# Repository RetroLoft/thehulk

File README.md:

# TheHulk

Network and SD card storage cartridge for the Atari ST, STE, Mega ST(E), TT and Falcon,
built around an ESP32-S3 and a Lattice iCE40UP5K FPGA. Successor of SideTNFS.

## Repository layout

| Path | Contents |
|---|---|
| `hardware/dev-v2/` | KiCad project and JLCPCB production files of the development board (ESP32-S3-DevKitC) |
| `hardware/prod-v2/` | KiCad project of the production board (ESP32-S3 module on the board, native USB, not ordered yet) |
| `hardware/prod-v3/` | prod-v2 plus switched 5 V on the micro-USB port, for USB keyboards and mice through an OTG adapter (not ordered yet, no firmware support yet) |
| `fpga/` | FPGA gateware (Verilog), pin constraints, simulation |
| `esp32/` | ESP32-S3 firmware (ESP-IDF); embeds the bitstream, GEMDRIVE and the built-in files of the flash drive |
| `atari/gemdrive/` | GEMDRIVE: the cartridge code the Atari runs (68000 assembly) |
| `atari/config/` | Configuration program for the Atari (GEM, C) |
| `atari/sting/` | `CART_NET.STX`: STinG driver for TheHulk's network bridge (C) |
| `atari/stingins/` | `STINGINS.TOS`: STinG installer on the flash drive, see [docs/NETWORK.md](docs/NETWORK.md) |
| `tools/` | Development helpers |
| `docs/` | Documentation: [hardware](docs/hardware-v2.md), [drives](docs/DRIVES.md), [internet with STinG](docs/NETWORK.md), [web page](docs/WEB.md), [cartridge emulator](docs/CARTRIDGE.md), [floppy emulator](docs/FLOPPY.md) |

## Building

```
./build.sh                     # everything
./build.sh flash /dev/ttyACM0  # and flash the ESP32, then open the serial monitor
./build.sh sim                 # gateware simulation
```

Requirements:
- FPGA: yosys, nextpnr-ice40 and icepack. `build.sh` installs the YoWASP builds from PyPI in
  `.venv-fpga` when no native tools are found.
- GEMDRIVE: `stcmd` from atarist-toolkit-docker (Docker image `logronoide/atarist-toolkit-docker`).
- Configuration program: `m68k-atari-mint-gcc` with gemlib. STinG driver and installer:
  `m68k-atari-mint-gcc`.
- ESP32: ESP-IDF 5.5 in `~/esp/esp-idf` (or set `IDF_PATH`).

## How it works

1. The ESP32 waits until the Atari powers the FPGA side of the board, then loads the
   bitstream into the FPGA over SPI (~50 ms at 20 MHz).
2. It writes the cartridge image (GEMDRIVE) into the FPGA's SPRAM and enables the cartridge.
   The FPGA keeps the data bus updated with the word at the current address; the data
   buffer is enabled in hardware by /ROM3 or /ROM4.
3. When the Atari is switched off, the ESP32 drives all FPGA lines low and waits for the
   next power-up.

Status LED (on the DevKitC): see [docs/WEB.md](docs/WEB.md#the-status-led). The web page
(`http://thehulk.local/`) shows the state and all settings; button 1 held 10 s switches AP
mode on, TheHulk's own Wi-Fi network for use away from home.

## License

GPL-3.0, see [LICENSE](LICENSE). GEMDRIVE is based on the SidecarTridge Multi-device
project by Diego Parrilla Santamaría (GOODDATA LABS SL).

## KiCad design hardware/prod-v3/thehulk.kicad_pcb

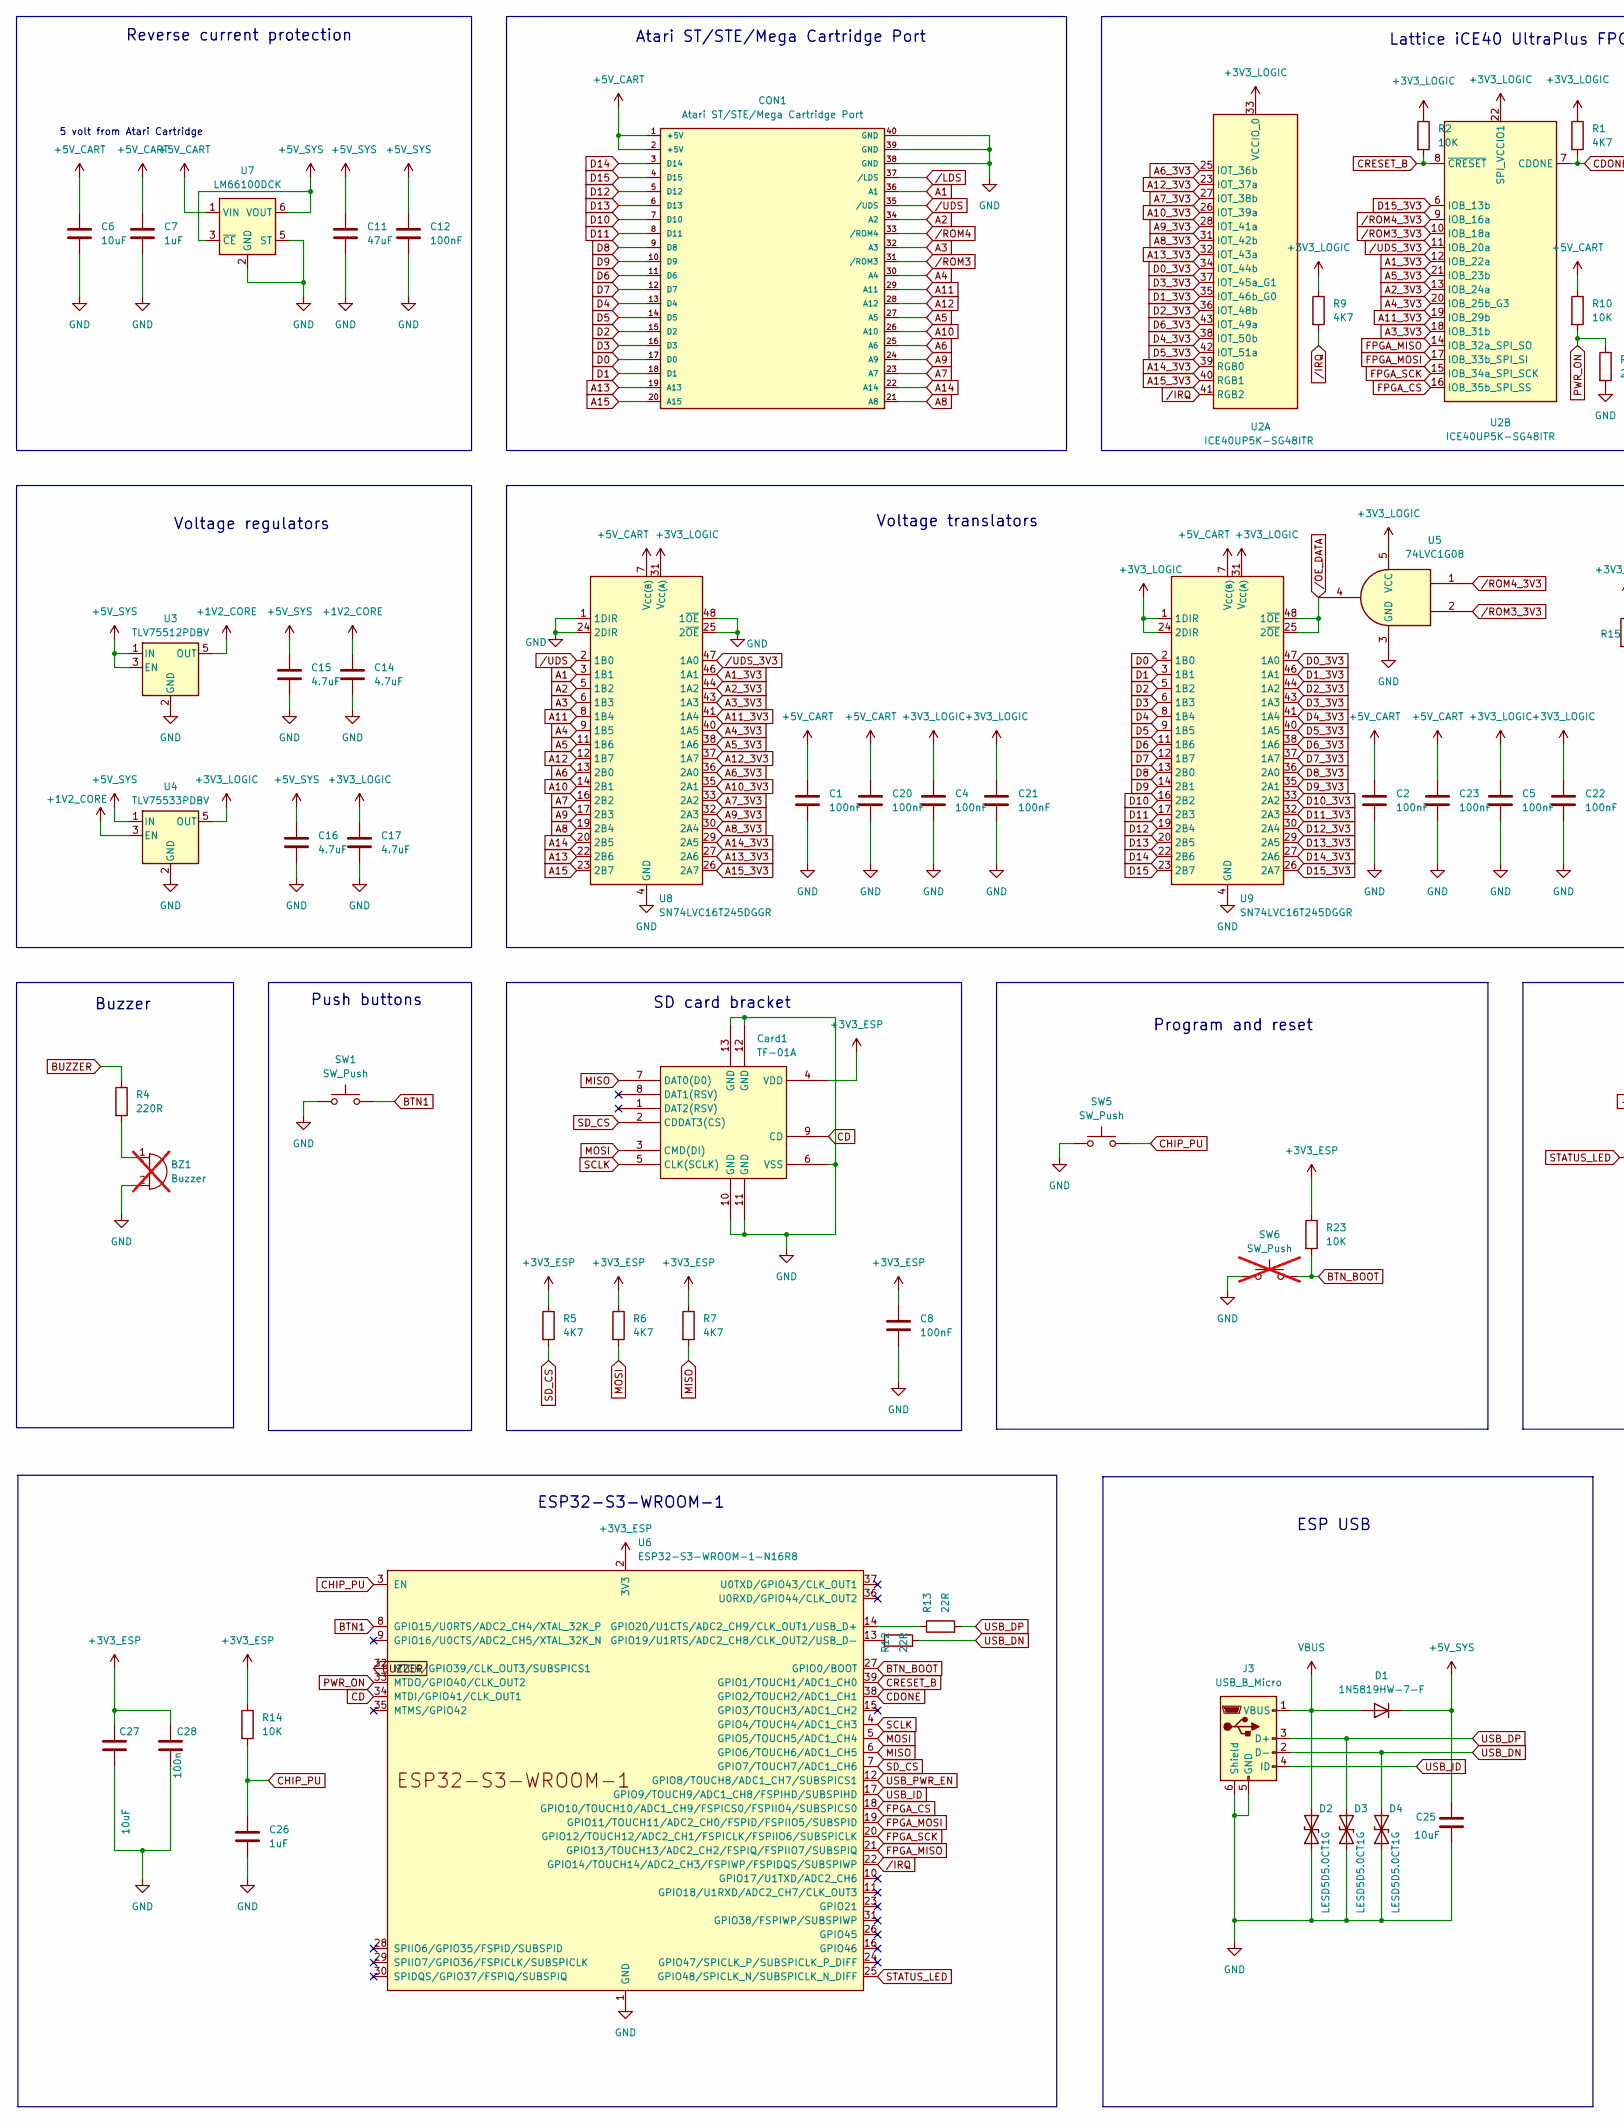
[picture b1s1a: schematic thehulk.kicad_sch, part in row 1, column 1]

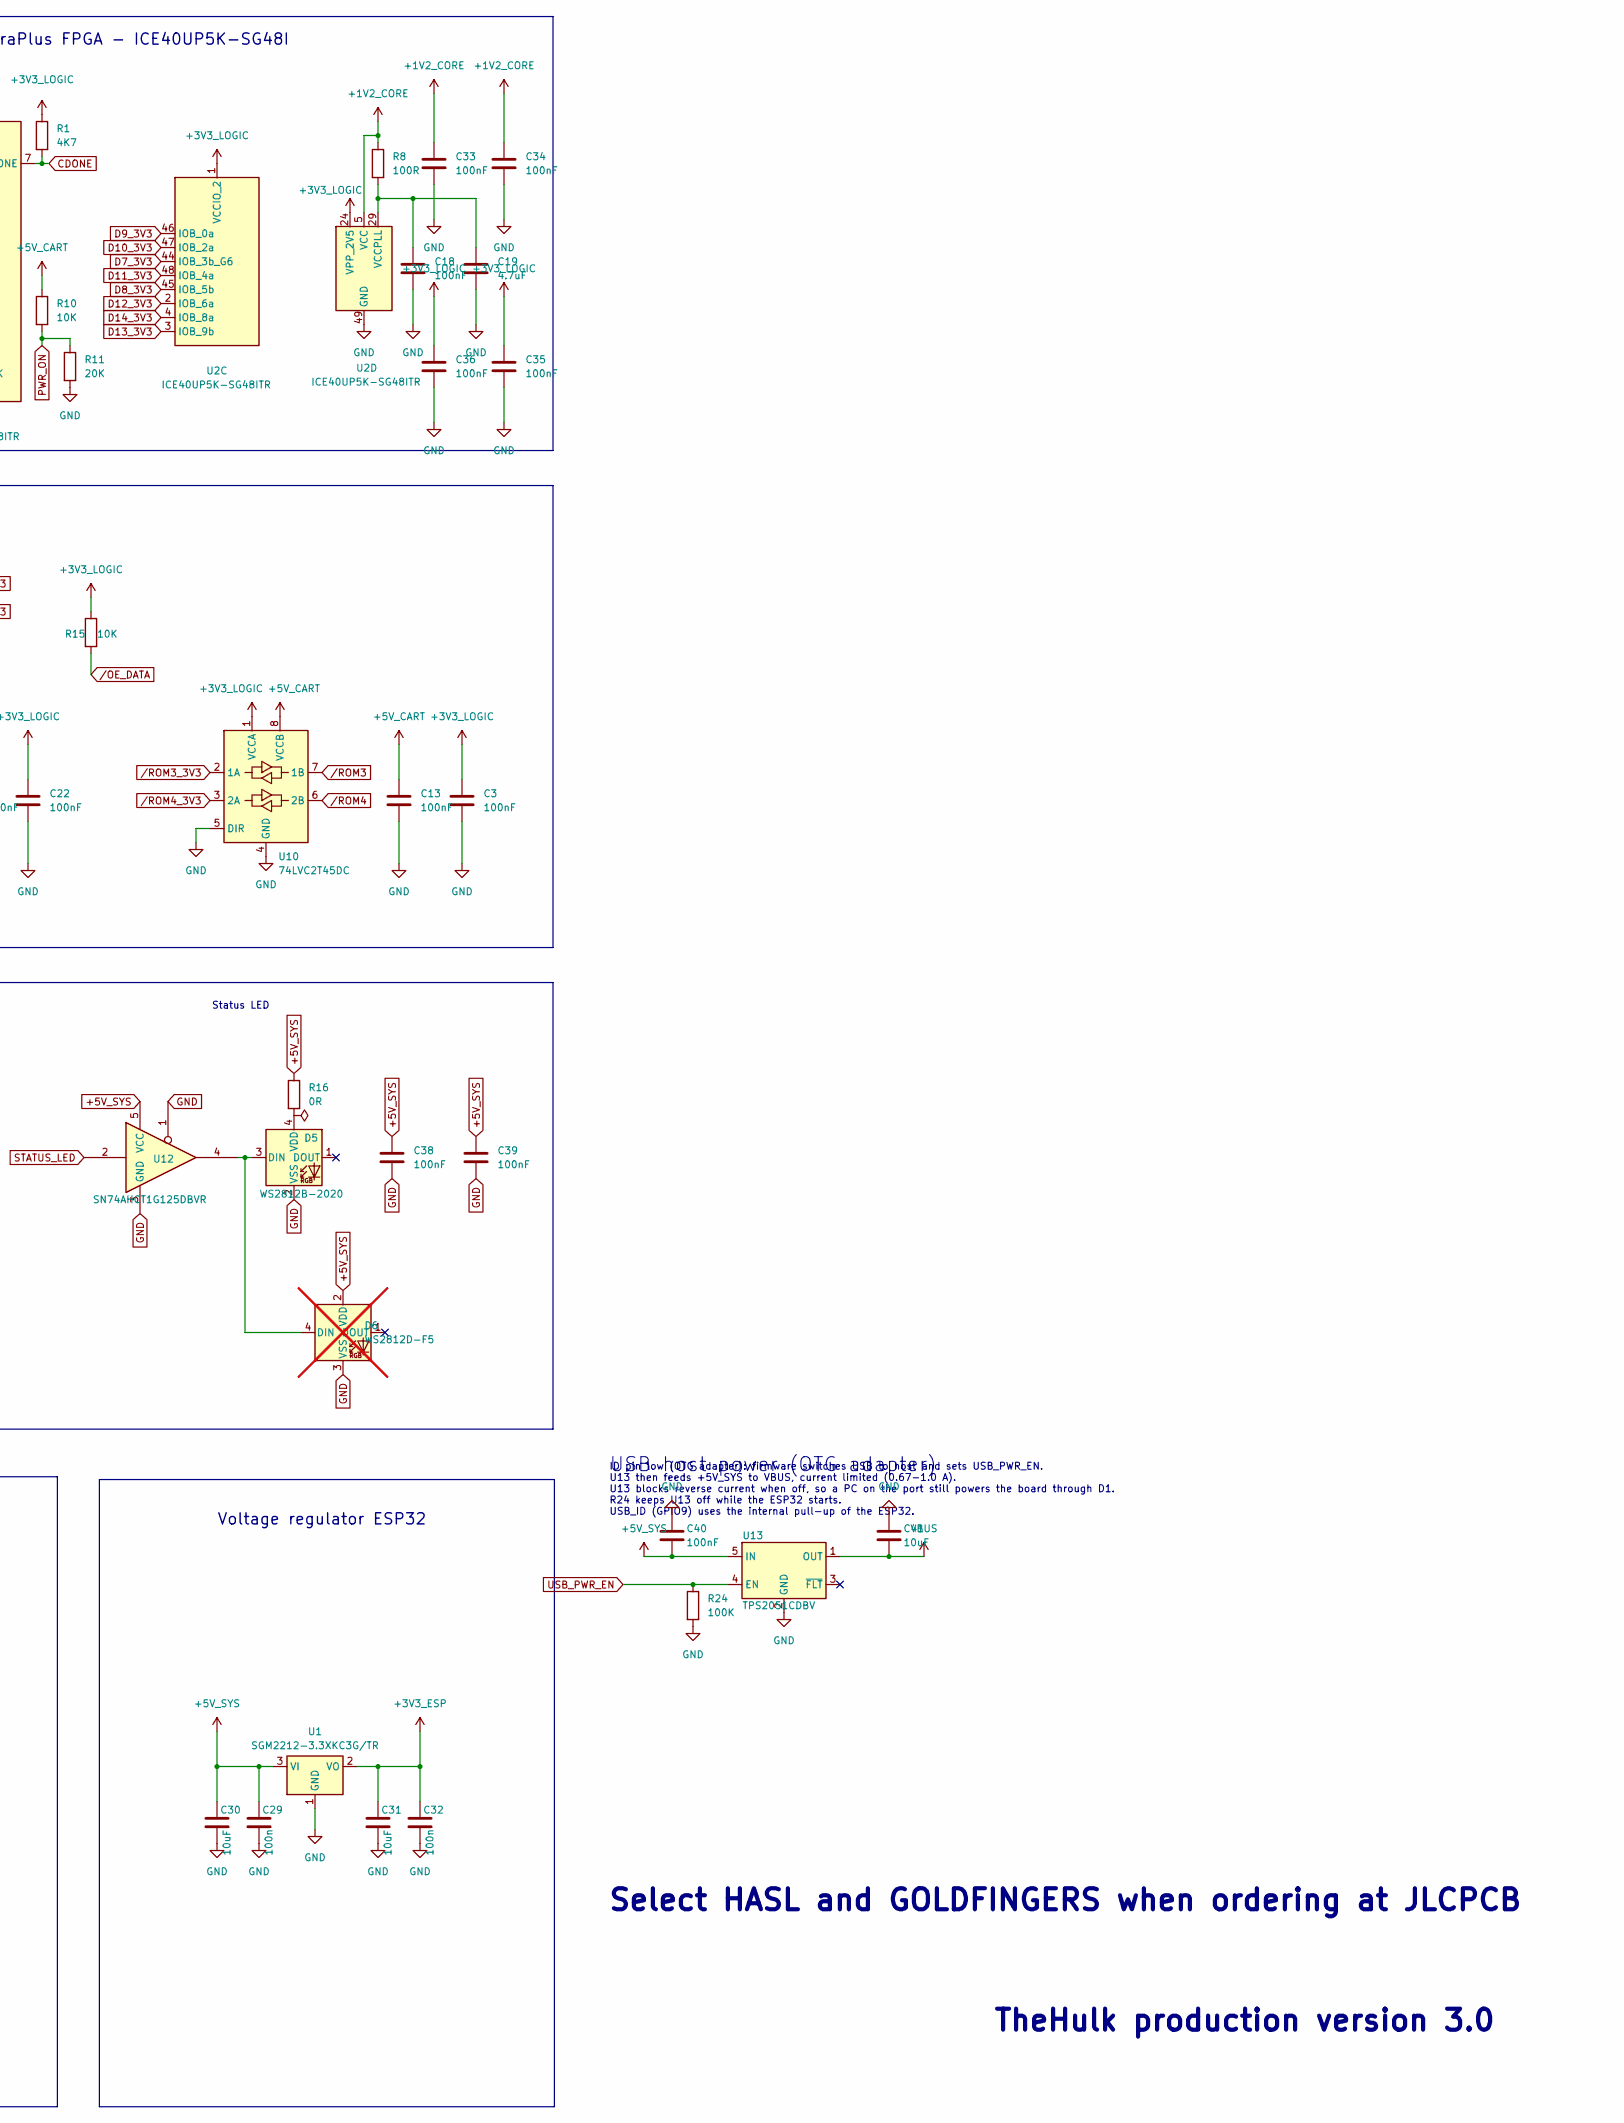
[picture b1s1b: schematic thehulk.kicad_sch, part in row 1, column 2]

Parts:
BZ1: Buzzer; Buzzer_12x9.5RM7.6; not fitted
C1, C2, C3, C4, C5, C8, C12, C13, C18, C20, C21, C22, C23, C33, C34, C35, C36, C38, C39, C40: 100nF; C_0402_1005Metric; LCSC Part C1525
C6, C25, C27, C30, C31, C41: 10uF; C_0603_1608Metric; LCSC Part C19702
C7: 1uF; C_0402_1005Metric; LCSC Part C52923
C11: 47uF; C_0805_2012Metric; LCSC Part C16780
C14, C15, C16, C17, C19: 4.7uF; C_0603_1608Metric; LCSC Part C19666
C26: 1uF; C_0603_1608Metric; LCSC Part C15849
C28, C29, C32: 100n; C_0603_1608Metric; LCSC Part C14663
CON1: Atari ST/STE/Mega Cartridge Port; Atari_Cart_Edge_40P_2mm
Card1: TF-01A; TF-SMD_TF-01A; MPN TF-01A; LCSC Part C91145
D1: 1N5819HW-7-F; D_SOD-123; LCSC Part C82544
D2, D3, D4: LESD5D5.0CT1G; D_SOD-523; LCSC Part C5199850
D5: WS2812B-2020; LED_WS2812B-2020_PLCC4_2.0x2.0mm; LCSC Part C52917434
D6: WS2812D-F5; LED_D5.0mm-4_WS2812D-F5; LCSC Part C190565; not fitted
J3: USB_B_Micro; USB_Micro-B_C10418; MPN Jing Extension 920-E52A2021S10100; LCSC Part C10418
R1, R5, R6, R7, R9: 4K7; R_0402_1005Metric; LCSC Part C25900
R2, R10: 10K; R_0402_1005Metric; LCSC Part C25744
R4: 220R; R_0603_1608Metric; LCSC Part C22962
R8: 100R; R_0402_1005Metric; LCSC Part C25076
R11: 20K; R_0402_1005Metric; LCSC Part C25765
R12, R13: 22R; R_0402_1005Metric; LCSC Part C25092
R14, R15, R23: 10K; R_0603_1608Metric; LCSC Part C25804
R16: 0R; R_0805_2012Metric; LCSC Part C17477
R24: 100K; R_0402_1005Metric; LCSC Part C25741
SW1: SW_Push; SW_Tactile_6x6_SMD_H9.5; MPN Kinghelm KH-6X6X9.5H-SMT (9.5 mm); LCSC Part C3038675
SW5: SW_Push; SW_SPST_B3U-1000P; LCSC Part C231329
SW6: SW_Push; SW_SPST_B3U-1000P; LCSC Part C231329; not fitted
U1: SGM2212-3.3XKC3G/TR; SOT-223-3_TabPin2; LCSC Part C3294699
U2: ICE40UP5K-SG48ITR; QFN-48-1EP_7x7mm_P0.5mm_EP5.6x5.6mm; LCSC Part C2678152
U3: TLV75512PDBV; SOT-23-5; LCSC Part C2877864
U4: TLV75533PDBV; SOT-23-5; LCSC Part C404027
U5: 74LVC1G08; SOT-23-5; LCSC Part C7666
U6: ESP32-S3-WROOM-1-N16R8; ESP32-S3-WROOM-1; LCSC Part C2913202
U7: LM66100DCK; SOT-363_SC-70-6; LCSC Part C2869734
U8, U9: SN74LVC16T245DGGR; TSSOP-48_6.1x12.5mm_P0.5mm; LCSC C148170
U10: 74LVC2T45DC; VSSOP-8_2.3x2mm_P0.5mm; LCSC Part C15741
U12: SN74AHCT1G125DBVR; SOT-23-5; LCSC Part C7484
U13: TPS2051CDBV; SOT-23-5; LCSC Part C129581

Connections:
+1V2_CORE: C14.1, C33.1, C34.1, R8.1, U2.5 (VCC), U2.30 (VCC), U3.5 (OUT), U4.3 (EN)
+3V3_ESP: C8.1, C27.1, C28.1, C31.1, C32.1, Card1.4 (VDD), R5.1, R6.1, R7.1, R14.1, R23.1, U1.2 (VO), U6.2 (3V3)
+3V3_LOGIC: C3.1, C4.1, C5.1, C17.1, C21.1, C22.1, C35.1, C36.1, R1.1, R2.1, R9.1, R15.1, U2.1 (VCCIO_2), U2.22 (SPI_VCCIO1), U2.24 (VPP_2V5), U2.33 (VCCIO_0), U4.5 (OUT), U5.5 (VCC), U8.31 (V_{CC(A)}), U8.42 (V_{CC(A)}), U9.1 (1DIR), U9.24 (2DIR), U9.31 (V_{CC(A)}), U9.42 (V_{CC(A)}), U10.1 (VCCA)
+5V_CART: C1.1, C2.1, C6.1, C7.1, C13.1, C20.1, C23.1, CON1.1 (+5V), CON1.2 (+5V), R10.1, U7.1 (VIN), U8.7 (V_{CC(B)}), U8.18 (V_{CC(B)}), U9.7 (V_{CC(B)}), U9.18 (V_{CC(B)}), U10.8 (VCCB)
+5V_SYS: C11.1, C12.1, C15.1, C16.1, C25.1, C29.1, C30.1, C38.1, C39.1, C40.2, D1.1 (K), D6.2 (VDD), R16.1, U1.3 (VI), U3.1 (IN), U3.3 (EN), U4.1 (IN), U7.3 (~CE), U7.6 (VOUT), U12.5 (VCC), U13.5 (IN)
A1: CON1.36 (A1), U8.3 (1B1)
A1_3V3: U2.12 (IOB_22a), U8.46 (1A1)
A2: CON1.34 (A2), U8.5 (1B2)
A2_3V3: U2.13 (IOB_24a), U8.44 (1A2)
A3: CON1.32 (A3), U8.6 (1B3)
A3_3V3: U2.18 (IOB_31b), U8.43 (1A3)
A4: CON1.30 (A4), U8.9 (1B5)
A4_3V3: U2.20 (IOB_25b_G3), U8.40 (1A5)
A5: CON1.27 (A5), U8.11 (1B6)
A5_3V3: U2.21 (IOB_23b), U8.38 (1A6)
A6: CON1.25 (A6), U8.13 (2B0)
A6_3V3: U2.25 (IOT_36b), U8.36 (2A0)
A7: CON1.23 (A7), U8.16 (2B2)
A7_3V3: U2.27 (IOT_38b), U8.33 (2A2)
A8: CON1.21 (A8), U8.19 (2B4)
A8_3V3: U2.31 (IOT_42b), U8.30 (2A4)
A9: CON1.24 (A9), U8.17 (2B3)
A9_3V3: U2.28 (IOT_41a), U8.32 (2A3)
A10: CON1.26 (A10), U8.14 (2B1)
A10_3V3: U2.26 (IOT_39a), U8.35 (2A1)
A11: CON1.29 (A11), U8.8 (1B4)
A11_3V3: U2.19 (IOB_29b), U8.41 (1A4)
A12: CON1.28 (A12), U8.12 (1B7)
A12_3V3: U2.23 (IOT_37a), U8.37 (1A7)
A13: CON1.19 (A13), U8.22 (2B6)
A13_3V3: U2.32 (IOT_43a), U8.27 (2A6)
A14: CON1.22 (A14), U8.20 (2B5)
A14_3V3: U2.39 (RGB0), U8.29 (2A5)
A15: CON1.20 (A15), U8.23 (2B7)
A15_3V3: U2.40 (RGB1), U8.26 (2A7)
BTN1: SW1.2, U6.8 (GPIO15/U0RTS/ADC2_CH4/XTAL_32K_P)
BTN_BOOT: R23.2, SW6.2, U6.27 (GPIO0/BOOT)
BUZZER: R4.1, U6.32 (MTCK/GPIO39/CLK_OUT3/SUBSPICS1)
CD: Card1.9 (CD), U6.34 (MTDI/GPIO41/CLK_OUT1)
CDONE: R1.2, U2.7 (CDONE), U6.38 (GPIO2/TOUCH2/ADC1_CH1)
CHIP_PU: C26.1, R14.2, SW5.2, U6.3 (EN)
CRESET_B: R2.2, U2.8 (~CRESET), U6.39 (GPIO1/TOUCH1/ADC1_CH0)
D0: CON1.17 (D0), U9.2 (1B0)
D0_3V3: U2.34 (IOT_44b), U9.47 (1A0)
D1: CON1.18 (D1), U9.3 (1B1)
D1_3V3: U2.35 (IOT_46b_G0), U9.46 (1A1)
D2: CON1.15 (D2), U9.5 (1B2)
D2_3V3: U2.36 (IOT_48b), U9.44 (1A2)
D3: CON1.16 (D3), U9.6 (1B3)
D3_3V3: U2.37 (IOT_45a_G1), U9.43 (1A3)
D4: CON1.13 (D4), U9.8 (1B4)
D4_3V3: U2.38 (IOT_50b), U9.41 (1A4)
D5: CON1.14 (D5), U9.9 (1B5)
D5_3V3: U2.42 (IOT_51a), U9.40 (1A5)
D6: CON1.11 (D6), U9.11 (1B6)
D6_3V3: U2.43 (IOT_49a), U9.38 (1A6)
D7: CON1.12 (D7), U9.12 (1B7)
D7_3V3: U2.44 (IOB_3b_G6), U9.37 (1A7)
D8: CON1.9 (D8), U9.13 (2B0)
D8_3V3: U2.45 (IOB_5b), U9.36 (2A0)
D9: CON1.10 (D9), U9.14 (2B1)
D9_3V3: U2.46 (IOB_0a), U9.35 (2A1)
D10: CON1.7 (D10), U9.16 (2B2)
D10_3V3: U2.47 (IOB_2a), U9.33 (2A2)
D11: CON1.8 (D11), U9.17 (2B3)
D11_3V3: U2.48 (IOB_4a), U9.32 (2A3)
D12: CON1.5 (D12), U9.19 (2B4)
D12_3V3: U2.2 (IOB_6a), U9.30 (2A4)
D13: CON1.6 (D13), U9.20 (2B5)
D13_3V3: U2.3 (IOB_9b), U9.29 (2A5)
D14: CON1.3 (D14), U9.22 (2B6)
D14_3V3: U2.4 (IOB_8a), U9.27 (2A6)
D15: CON1.4 (D15), U9.23 (2B7)
D15_3V3: U2.6 (IOB_13b), U9.26 (2A7)
FPGA_CS: U2.16 (IOB_35b_SPI_SS), U6.18 (GPIO10/TOUCH10/ADC1_CH9/FSPICS0/FSPIIO4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)
FPGA_MISO: U2.14 (IOB_32a_SPI_SO), U6.21 (GPIO13/TOUCH13/ADC2_CH2/FSPIQ/FSPIIO7/S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)
FPGA_MOSI: U2.17 (IOB_33b_SPI_SI), U6.19 (GPIO11/TOUCH11/ADC2_CH0/FSPID/FSPIIO5/S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)
FPGA_SCK: U2.15 (IOB_34a_SPI_SCK), U6.20 (GPIO12/TOUCH12/ADC2_CH1/FSPICLK/FSPIIO6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)
GND: BZ1.2 (-), C1.2, C2.2, C3.2, C4.2, C5.2, C6.2, C7.2, C8.2, C11.2, C12.2, C13.2, C14.2, C15.2, C16.2, C17.2, C18.2, C19.2, C20.2, C21.2, C22.2, C23.2, C25.2, C26.2, C27.2, C28.2, C29.2, C30.2, C31.2, C32.2, C33.2, C34.2, C35.2, C36.2, C38.2, C39.2, C40.1, C41.1, CON1.38 (GND), CON1.39 (GND), CON1.40 (GND), Card1.6 (VSS), Card1.10 (GND), Card1.11 (GND), Card1.12 (GND), Card1.13 (GND), D2.1 (A1), D3.1 (A1), D4.1 (A1), D5.2 (VSS), D6.3 (VSS), J3.5 (GND), J3.6 (Shield), R11.2, R24.2, SW1.1, SW5.1, SW6.1, U1.1 (GND), U2.49 (GND), U3.2 (GND), U4.2 (GND), U5.3 (GND), U6.1 (GND), U6.40 (GND), U6.41 (GND), U7.2 (GND), U7.5 (ST), U8.1 (1DIR), U8.4 (GND), U8.10 (GND), U8.15 (GND), U8.21 (GND), U8.24 (2DIR), U8.25 (2~OE), U8.28 (GND), U8.34 (GND), U8.39 (GND), U8.45 (GND), U8.48 (1~OE), U9.4 (GND), U9.10 (GND), U9.15 (GND), U9.21 (GND), U9.28 (GND), U9.34 (GND), U9.39 (GND), U9.45 (GND), U10.4 (GND), U10.5 (DIR), U12.1, U12.3 (GND), U13.2 (GND)
MISO: Card1.7 (DAT0(D0)), R7.2, U6.6 (GPIO6/TOUCH6/ADC1_CH5)
MOSI: Card1.3 (CMD(DI)), R6.2, U6.5 (GPIO5/TOUCH5/ADC1_CH4)
unnamed: BZ1.1 (+), R4.2
unnamed: D5.3 (DIN), D6.4 (DIN), U12.4
unnamed: D5.4 (VDD), R16.2
unnamed: C18.1, C19.1, R8.2, U2.29 (VCCPLL)
unnamed: R12.1, U6.13 (GPIO19/U1RTS/ADC2_CH8/CLK_OUT2/USB_D-)
unnamed: R13.1, U6.14 (GPIO20/U1CTS/ADC2_CH9/CLK_OUT1/USB_D+)
PWR_ON: R10.2, R11.1, U6.33 (MTDO/GPIO40/CLK_OUT2)
SCLK: Card1.5 (CLK(SCLK)), U6.4 (GPIO4/TOUCH4/ADC1_CH3)
SD_CS: Card1.2 (CDDAT3(CS)), R5.2, U6.7 (GPIO7/TOUCH7/ADC1_CH6)
STATUS_LED: U6.25 (GPIO48/SPICLK_N/SUBSPICLK_N_DIFF), U12.2
USB_DN: D4.2 (A2), J3.2 (D-), R12.2
USB_DP: D3.2 (A2), J3.3 (D+), R13.2
USB_ID: J3.4 (ID), U6.17 (GPIO9/TOUCH9/ADC1_CH8/FSPIHD/SUBSPIHD)
USB_PWR_EN: R24.1, U6.12 (GPIO8/TOUCH8/ADC1_CH7/SUBSPICS1), U13.4 (EN)
VBUS: C41.2, D1.2 (A), D2.2 (A2), J3.1 (VBUS), U13.1 (OUT)
/IRQ: R9.2, U2.41 (RGB2), U6.22 (GPIO14/TOUCH14/ADC2_CH3/FSPIWP/FSPIDQS/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)
/LDS: CON1.37 (/LDS)
/OE_DATA: R15.2, U5.4, U9.25 (2~OE), U9.48 (1~OE)
/ROM3: CON1.31 (/ROM3), U10.7 (1B)
/ROM3_3V3: U2.10 (IOB_18a), U5.2, U10.2 (1A)
/ROM4: CON1.33 (/ROM4), U10.6 (2B)
/ROM4_3V3: U2.9 (IOB_16a), U5.1, U10.3 (2A)
/UDS: CON1.35 (/UDS), U8.2 (1B0)
/UDS_3V3: U2.11 (IOB_20a), U8.47 (1A0)

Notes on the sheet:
Select HASL and GOLDFINGERS when ordering at JLCPCB
5 volt from Atari Cartridge
Buzzer
Reverse current protection
ESP USB
TheHulk production version 3.0
SD card bracket
Program and reset
Voltage regulators
Push buttons
Lattice iCE40 UltraPlus FPGA - ICE40UP5K-SG48I
Voltage translators
ESP32-S3-WROOM-1
Voltage regulator ESP32
Atari ST/STE/Mega Cartridge Port
Status LED
USB host power (OTG adapter)
ID pin low (OTG adapter): firmware switches USB to host and sets USB_PWR_EN. U13 then feeds +5V_SYS to VBUS, current limited (0.67-1.0 A). U13 blocks reverse current when off, so a PC on the port still powers the board through D1. R24 keeps U13 off while the ESP32 starts. USB_ID (GPIO9) uses the in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

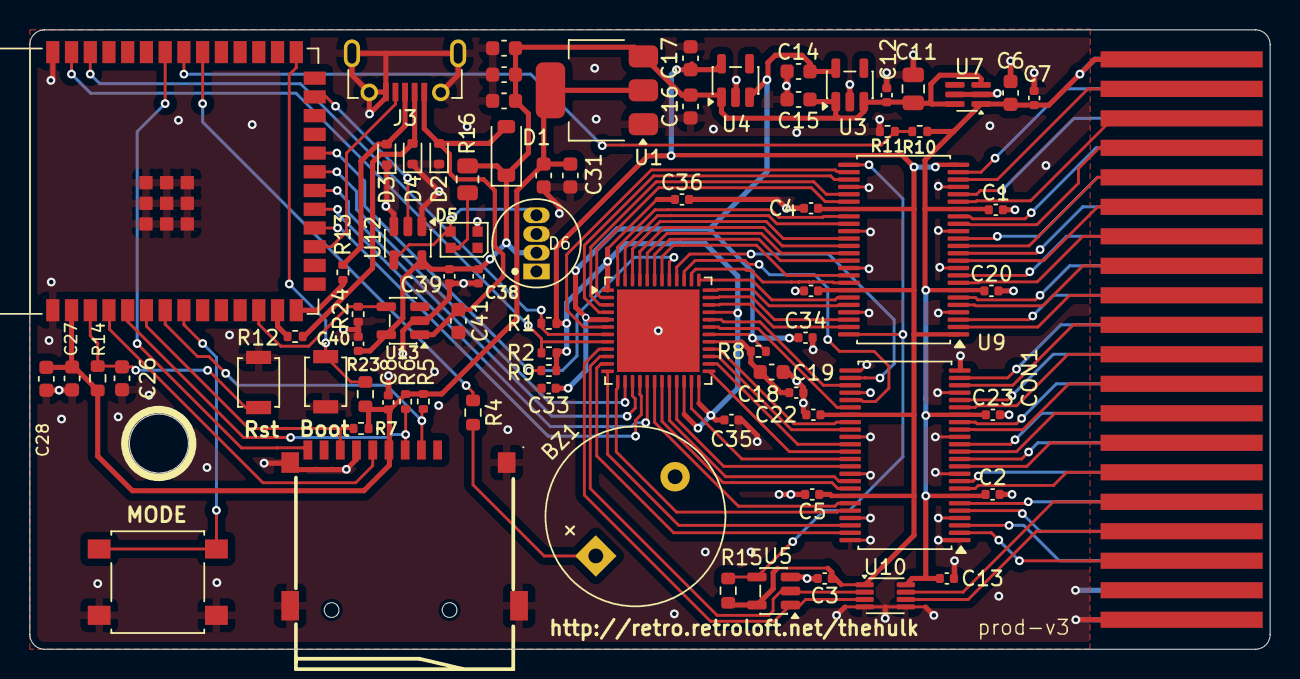
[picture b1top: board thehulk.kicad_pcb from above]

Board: 2 copper layers, 84.1 x 42.0 mm, 79 parts (0 on the bottom side), 104 nets.

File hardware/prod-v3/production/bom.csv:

Designator,Footprint,Quantity,Value,LCSC Part #
"C1, C12, C13, C18, C2, C20, C21, C22, C23, C3, C33, C34, C35, C36, C38, C39, C4, C40, C5, C8",0402,20,100nF,C1525
C11,0805,1,47uF,C16780
"C14, C15, C16, C17, C19",0603,5,4.7uF,C19666
"C25, C27, C30, C31, C41, C6",0603,6,10uF,C19702
C26,0603,1,1uF,C15849
"C28, C29, C32",0603,3,100n,C14663
C7,0402,1,1uF,C52923
CARD1,TF-SMD_TF-01A,1,TF-01A,C91145
D1,D_SOD-123,1,1N5819HW-7-F,C82544
"D2, D3, D4",D_SOD-523,3,LESD5D5.0CT1G,C5199850
D5,LED_WS2812B-2020_PLCC4_2.0x2.0mm,1,WS2812B-2020,C52917434
J3,USB_Micro-B_C10418,1,USB_B_Micro,C10418
"R1, R5, R6, R7, R9",0402,5,4K7,C25900
"R10, R2",0402,2,10K,C25744
R11,0402,1,20K,C25765
"R12, R13",0402,2,22R,C25092
"R14, R15, R23",0603,3,10K,C25804
R16,0805,1,0R,C17477
R24,0402,1,100K,C25741
R4,0603,1,220R,C22962
R8,0402,1,100R,C25076
SW1,SW_Tactile_6x6_SMD_H9.5,1,SW_Push,C3038675
SW5,SW_SPST_B3U-1000P,1,SW_Push,C231329
U1,SOT-223-3_TabPin2,1,SGM2212-3.3XKC3G/TR,C3294699
U10,VSSOP-8_2.3x2mm_P0.5mm,1,74LVC2T45DC,C15741
U12,SOT-23-5,1,SN74AHCT1G125DBVR,C7484
U13,SOT-23-5,1,TPS2051CDBV,C129581
U2,QFN-48-1EP_7x7mm_P0.5mm_EP5.6x5.6mm,1,ICE40UP5K-SG48ITR,C2678152
U3,SOT-23-5,1,TLV75512PDBV,C2877864
U4,SOT-23-5,1,TLV75533PDBV,C404027
U5,SOT-23-5,1,74LVC1G08,C7666
U6,ESP32-S3-WROOM-1,1,ESP32-S3-WROOM-1-N16R8,C2913202
U7,SOT-363_SC-70-6,1,LM66100DCK,C2869734
"U8, U9",TSSOP-48_6.1x12.5mm_P0.5mm,2,SN74LVC16T245DGGR,C148170

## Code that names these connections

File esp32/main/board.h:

// TheHulk board v2: ESP32-S3-DevKitC-1 (N16R8) pin assignment
// (hardware/dev-v2/thehulk.kicad_sch)
#pragma once

#include "driver/gpio.h"
#include "driver/spi_master.h"

// FPGA configuration and SPI link (IOMUX pins of SPI2/FSPI)
#define PIN_FPGA_CRESET   GPIO_NUM_1
#define PIN_FPGA_CDONE    GPIO_NUM_2
#define PIN_FPGA_CS       GPIO_NUM_10   // SPI_SS (held low while loading the bitstream)
#define PIN_FPGA_MOSI     GPIO_NUM_11   // SPI_SI
#define PIN_FPGA_SCK      GPIO_NUM_12
#define PIN_FPGA_MISO     GPIO_NUM_13   // SPI_SO
#define PIN_FPGA_IRQ      GPIO_NUM_14   // /IRQ from the FPGA, pull-up R9
#define FPGA_SPI_HOST     SPI2_HOST

// +3V3_LOGIC through R10: high when the Atari powers the FPGA side of the board
#define PIN_PWR_ON        GPIO_NUM_40

// Push buttons, active low (no external pull-ups)
#define PIN_BTN1          GPIO_NUM_15
#define PIN_BTN2          GPIO_NUM_16
#define PIN_BTN3          GPIO_NUM_8
#define PIN_BTN4          GPIO_NUM_9

// On-board WS2812 RGB LED of the DevKitC (status)
#define PIN_STATUS_LED    GPIO_NUM_48

// microSD (push-push socket) and display share an SPI bus
#define PIN_SPI_SCLK      GPIO_NUM_4
#define PIN_SPI_MOSI      GPIO_NUM_5
#define PIN_SPI_MISO      GPIO_NUM_6
#define PIN_SD_CS         GPIO_NUM_7
#define PIN_SD_CD         GPIO_NUM_41   // card detect, internal pull-up
#define PIN_DISP_CS       GPIO_NUM_18
#define PIN_DISP_DC       GPIO_NUM_21
#define PIN_DISP_RST      GPIO_NUM_47
#define PIN_DISP_BL       GPIO_NUM_38

#define PIN_RST_ST        GPIO_NUM_17   // Atari reset via Q2 (high = reset), J4 optional
#define PIN_BUZZER        GPIO_NUM_39
